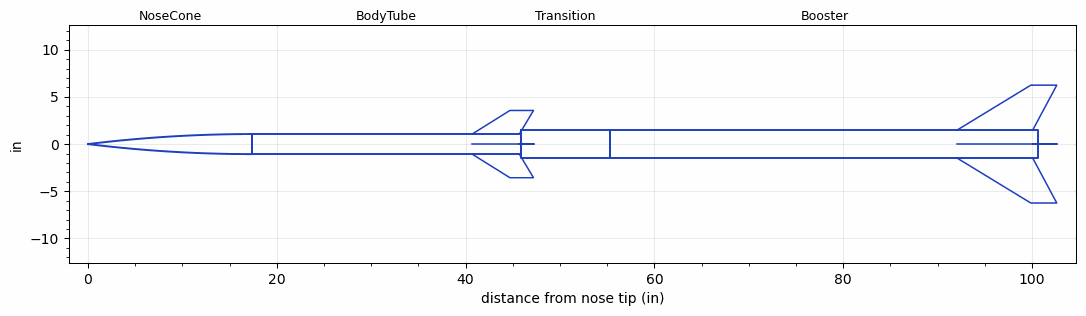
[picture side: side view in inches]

<RASAeroDocument>
 <FileVersion>2</FileVersion>
 <RocketDesign>
  <NoseCone>
   <Length>17.375</Length>
   <Diameter>2.125</Diameter>
   <Shape>Tangent Ogive</Shape>
   <Location>0</Location>
  </NoseCone>
  <BodyTube>
   <Length>28.443</Length>
   <Diameter>2.125</Diameter>
   <Location>17.375</Location>
   <Fin>
    <Count>4</Count>
    <Chord>5</Chord>
    <Span>2.5</Span>
    <SweepDistance>4</SweepDistance>
    <TipChord>2.5</TipChord>
    <Thickness>0.125</Thickness>
    <LERadius>1</LERadius>
    <Location>5.125</Location>
    <AirfoilSection>Hexagonal</AirfoilSection>
    <FX1>2</FX1>
    <FX3>2</FX3>
   </Fin>
  </BodyTube>
  <Transition>
   <Length>9.5</Length>
   <Diameter>2.985</Diameter>
   <Location>45.818</Location>
   <RearDiameter>2.985</RearDiameter>
  </Transition>
  <Booster>
   <Length>45.366</Length>
   <Diameter>2.985</Diameter>
   <InsideDiameter>2.985</InsideDiameter>
   <Location>55.318</Location>
   <ShoulderLength>0</ShoulderLength>
   <Fin>
    <Count>4</Count>
    <Chord>8</Chord>
    <Span>4.75</Span>
    <SweepDistance>7.794</SweepDistance>
    <TipChord>2.75</TipChord>
    <Thickness>0.18</Thickness>
    <LERadius>1</LERadius>
    <Location>8.6</Location>
    <AirfoilSection>Hexagonal</AirfoilSection>
    <FX1>2</FX1>
    <FX3>2</FX3>
   </Fin>
  </Booster>
  <Surface>Smooth Paint</Surface>
  <ModifiedBarrowman>True</ModifiedBarrowman>
  <Turbulence>True</Turbulence>
  <UseBooster1>False</UseBooster1>
  <UseBooster2>False</UseBooster2>
 </RocketDesign>
 <LaunchSite>
  <Altitude>1344</Altitude>
  <Pressure>0</Pressure>
  <RodAngle>0</RodAngle>
  <RodLength>10</RodLength>
  <Temperature>74</Temperature>
  <WindSpeed>0</WindSpeed>
 </LaunchSite>
 <Recovery>
  <Altitude1>1000</Altitude1>
  <Altitude2>1000</Altitude2>
  <DeviceType1>None</DeviceType1>
  <DeviceType2>None</DeviceType2>
  <Event1>False</Event1>
  <Event2>False</Event2>
  <Size1>1</Size1>
  <Size2>1</Size2>
  <EventType1>None</EventType1>
  <EventType2>None</EventType2>
  <CD1>1.33</CD1>
  <CD2>1.33</CD2>
 </Recovery>
 <SimulationList>
  <Simulation>
   <SustainerEngine>K2144  (SRT)</SustainerEngine>
   <SustainerLaunchWt>5.51</SustainerLaunchWt>
   <SustainerCG>29.52</SustainerCG>
   <SustainerIgnitionDelay>0.5</SustainerIgnitionDelay>
   <Booster1Engine>M3464LB  (Loki)</Booster1Engine>
   <Booster1LaunchWt>24.75</Booster1LaunchWt>
   <Booster1SeparationDelay>0</Booster1SeparationDelay>
   <Booster1IgnitionDelay>0</Booster1IgnitionDelay>
   <Booster1CG>68.32</Booster1CG>
   <IncludeBooster1>True</IncludeBooster1>
   <Booster2Delay>0</Booster2Delay>
   <IncludeBooster2>False</IncludeBooster2>
   <TimetoApogee>26.35044</TimetoApogee>
   <MaxAltitude>18493.55</MaxAltitude>
   <MaxVelocity>2768.914</MaxVelocity>
  </Simulation>
 </SimulationList>
</RASAeroDocument>
